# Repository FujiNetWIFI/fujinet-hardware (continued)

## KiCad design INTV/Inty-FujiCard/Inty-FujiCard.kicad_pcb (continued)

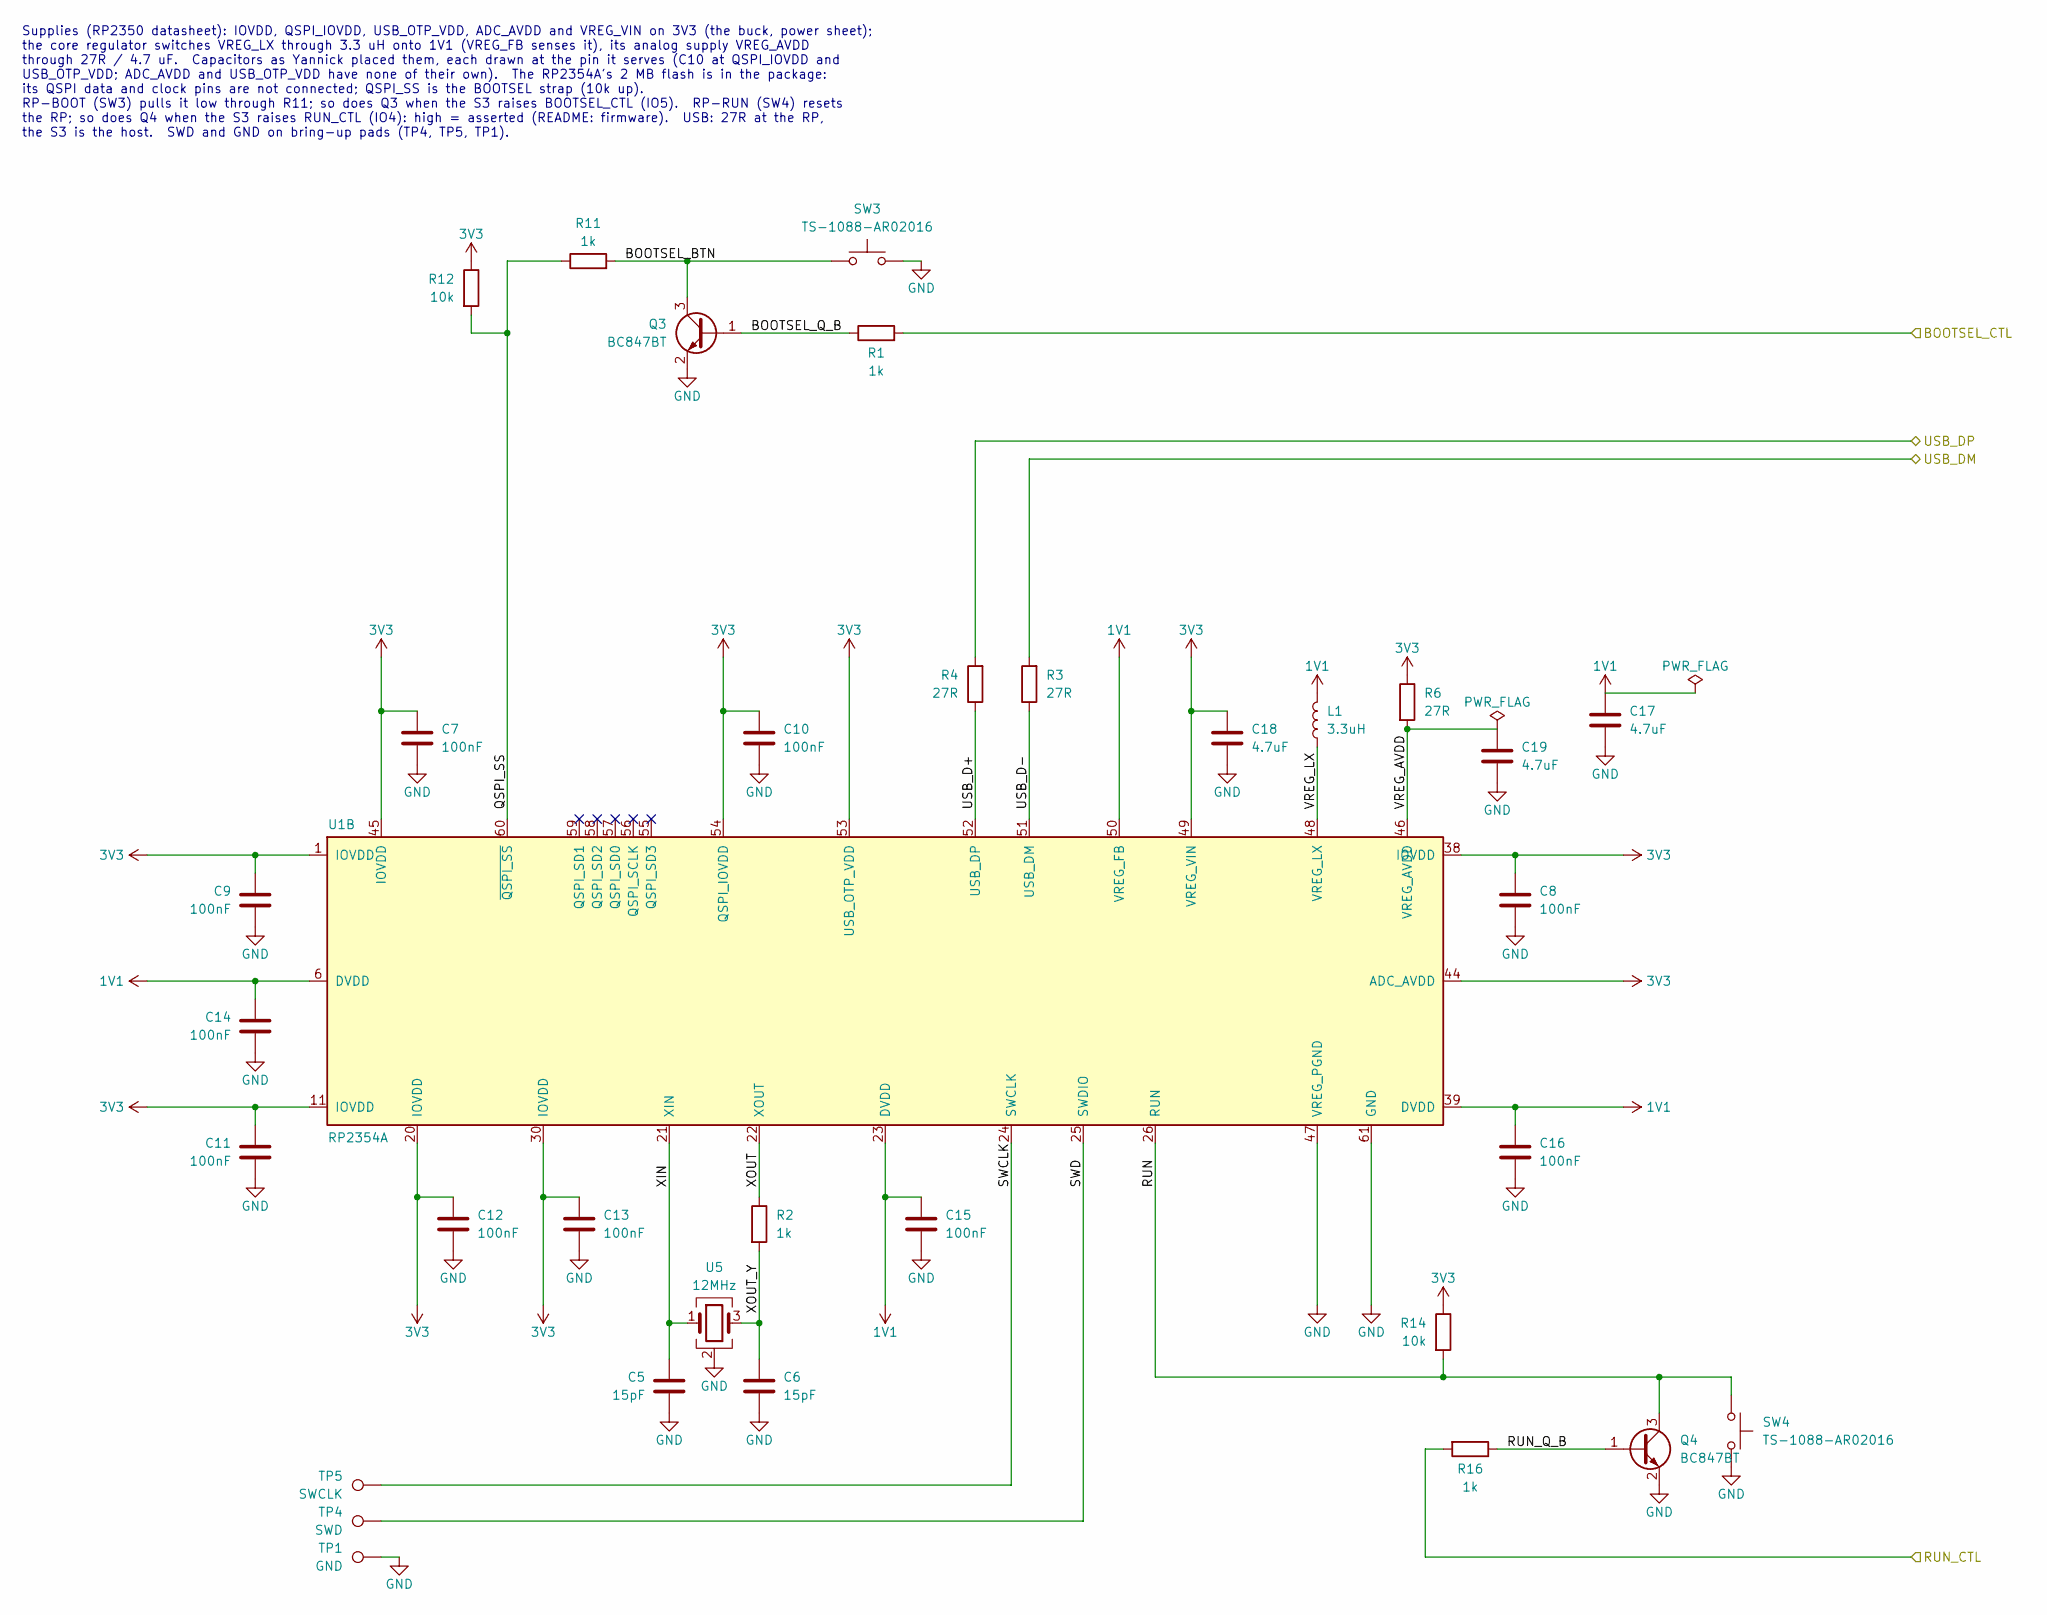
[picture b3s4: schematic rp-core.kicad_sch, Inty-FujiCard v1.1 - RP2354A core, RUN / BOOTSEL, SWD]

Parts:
C5, C6: 15pF; C0402; MPN 0402CG150J500NT; LCSC C1548
C7, C8, C9, C10, C11, C12, C13, C14, C15, C16: 100nF; C0402; MPN CL05B104KO5NNNC; LCSC C1525
C17, C18: 4.7uF; C0603; MPN CL10A475KO8NNNC; LCSC C19666
C19: 4.7uF; C0402; MPN CL05A475MP5NRNC; LCSC C23733
L1: 3.3uH; IND-SMD_L2.0-W1.6_AOTA-B201610S3R3-101-T; MPN AOTA-B201610S3R3-101-T; LCSC C42411119
Q3, Q4: BC847BT; SOT-523-3_L1.6-W0.8-P1.00-LS1.6-BR; MPN BC847BT; LCSC C5186022
R1, R2, R11, R16: 1k; R0402; MPN 0402WGF1001TCE; LCSC C11702
R3, R4, R6: 27R; R0402; MPN 0402WGF270JTCE; LCSC C25100
R12, R14: 10k; R0402; MPN 0402WGF1002TCE; LCSC C25744
SW3, SW4: TS-1088-AR02016; SW-SMD_L3.9-W3.0-P4.45; MPN TS-1088-AR02016; LCSC C720477
TP1: GND; TESTPOINT_PAD_D1.5MM
TP4: SWD; TESTPOINT_PAD_D1.5MM
TP5: SWCLK; TESTPOINT_PAD_D1.5MM
U1: RP2354A; QFN-60_L7.0-W7.0-P0.40-TL-EP3.4; MPN RP2354A; LCSC C41378174
U5: 12MHz; CRYSTAL-SMD_4P-L3.2-W2.5-BL; MPN ABM8-272-T3; LCSC C20625731

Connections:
1V1: C14.2, C15.2, C16.2, C17.2, L1.2, U1.6 (DVDD), U1.23 (DVDD), U1.39 (DVDD), U1.50 (VREG_FB)
3V3: C7.2, C8.2, C9.2, C10.2, C11.2, C12.2, C13.2, C18.2, R6.1, R12.1, R14.1, U1.1 (IOVDD), U1.11 (IOVDD), U1.20 (IOVDD), U1.30 (IOVDD), U1.38 (IOVDD), U1.44 (ADC_AVDD), U1.45 (IOVDD), U1.49 (VREG_VIN), U1.53 (USB_OTP_VDD), U1.54 (QSPI_IOVDD); also elsewhere on the board
/BOOTSEL_CTL: R1.2; also elsewhere on the board
/RUN_CTL: R16.2; also elsewhere on the board
/USB_DM: R3.2; also elsewhere on the board
/USB_DP: R4.2; also elsewhere on the board
/rp-core/BOOTSEL_BTN: Q3.3 (C), R11.2, SW3.1
/rp-core/BOOTSEL_Q_B: Q3.1 (B), R1.1
/rp-core/QSPI_SS: R11.1, R12.2, U1.60 (~QSPI_SS)
/rp-core/RUN: Q4.3 (C), R14.2, SW4.1, U1.26 (RUN)
/rp-core/RUN_Q_B: Q4.1 (B), R16.1
/rp-core/SWCLK: TP5.1, U1.24 (SWCLK)
/rp-core/SWD: TP4.1, U1.25 (SWDIO)
/rp-core/USB_D+: R4.1, U1.52 (USB_DP)
/rp-core/USB_D-: R3.1, U1.51 (USB_DM)
/rp-core/VREG_AVDD: C19.2, R6.2, U1.46 (VREG_AVDD)
/rp-core/VREG_LX: L1.1, U1.48 (VREG_LX)
/rp-core/XIN: C5.2, U1.21 (XIN), U5.1
/rp-core/XOUT: R2.1, U1.22 (XOUT)
/rp-core/XOUT_Y: C6.2, R2.2, U5.3
GND: C5.1, C6.1, C7.1, C8.1, C9.1, C10.1, C11.1, C12.1, C13.1, C14.1, C15.1, C16.1, C17.1, C18.1, C19.1, Q3.2 (E), Q4.2 (E), SW3.2, SW4.2, TP1.1, U1.47 (VREG_PGND), U1.61 (GND), U5.2 (G), U5.4 (G); also elsewhere on the board

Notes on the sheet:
Supplies (RP2350 datasheet): IOVDD, QSPI_IOVDD, USB_OTP_VDD, ADC_AVDD and VREG_VIN on 3V3 (the buck, power sheet); the core regulator switches VREG_LX through 3.3 uH onto 1V1 (VREG_FB senses it), its analog supply VREG_AVDD through 27R / 4.7 uF. Capacitors as Yannick placed them, each drawn at the 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

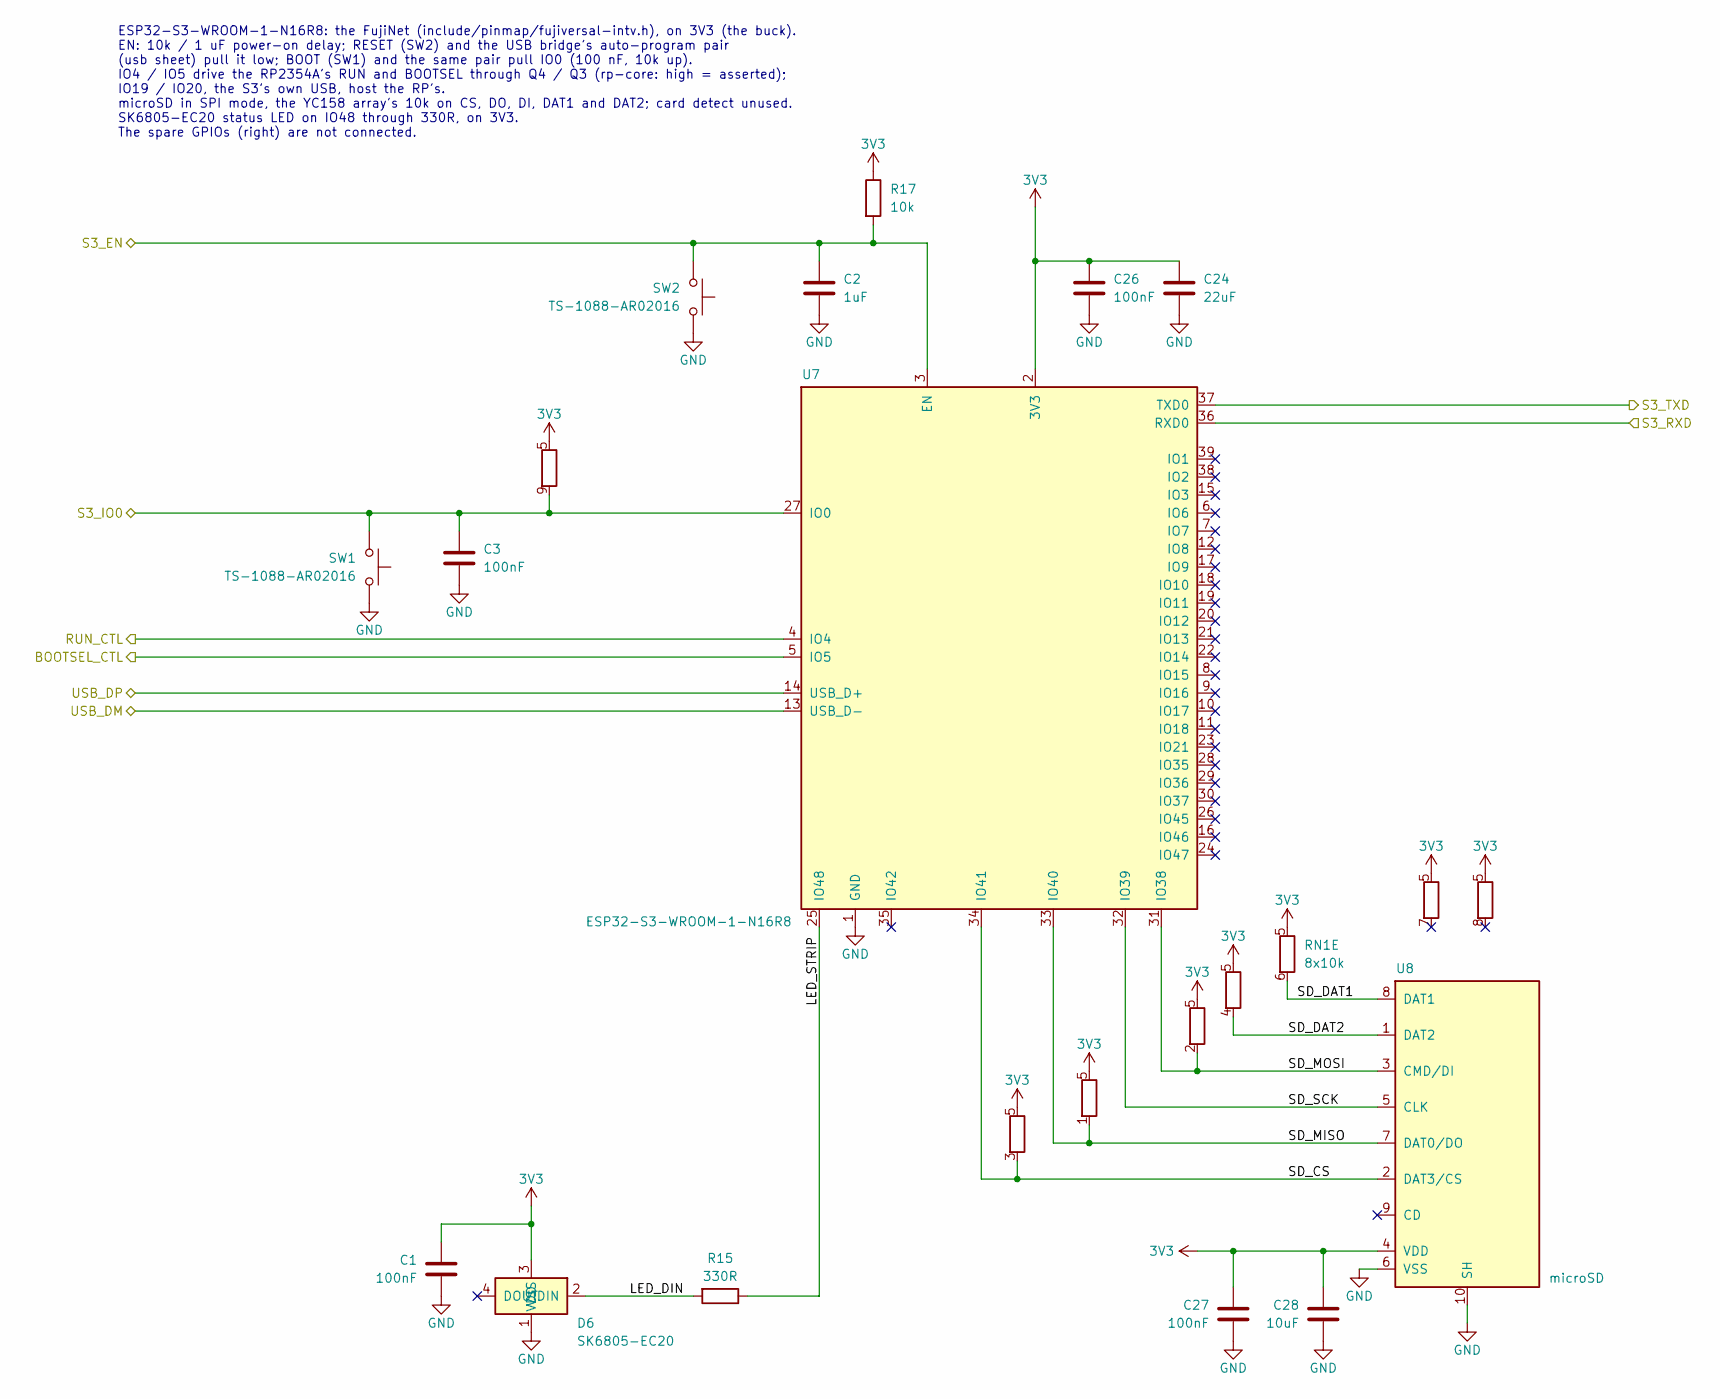
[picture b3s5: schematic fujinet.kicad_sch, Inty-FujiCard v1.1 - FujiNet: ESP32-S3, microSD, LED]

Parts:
C1, C3, C26, C27: 100nF; C0402; MPN CL05B104KO5NNNC; LCSC C1525
C2: 1uF; C0402; MPN CL05A105KA5NQNC; LCSC C52923
C24: 22uF; C0603; MPN CL10A226MQ8NRNC; LCSC C59461
C28: 10uF; C0603; MPN CL10A106KP8NNNC; LCSC C19702
D6: SK6805-EC20; LED-SMD_4P-L2.0-W2.0-TL_J-ST2020RGB-IC-P4-5-SO1; MPN SK6805-EC20; LCSC C2890036
R15: 330R; R0402; MPN 0402WGF3300TCE; LCSC C25104
R17: 10k; R0402; MPN 0402WGF1002TCE; LCSC C25744
RN1: 8x10k; RES-ARRAY-SMD_1206-L3.2-W1.6-P0.64; MPN YC158TJR-0710KL; LCSC C309679
SW1, SW2: TS-1088-AR02016; SW-SMD_L3.9-W3.0-P4.45; MPN TS-1088-AR02016; LCSC C720477
U7: ESP32-S3-WROOM-1-N16R8; WIRELM-SMD_ESP32-S3-WROOM-1; MPN ESP32-S3-WROOM-1-N16R8; LCSC C2913202
U8: microSD; SIM-SMD_LX_XDFP-0090-012; MPN TF-CARD-9P; LCSC C53144700

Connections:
3V3: C1.2, C24.2, C26.2, C27.2, C28.1, D6.3 (VDD), R17.1, RN1.5 (COM), RN1.10 (COM), U7.2 (3V3), U8.4 (VDD); also elsewhere on the board
/BOOTSEL_CTL: U7.5 (IO5); also elsewhere on the board
/RUN_CTL: U7.4 (IO4); also elsewhere on the board
/S3_EN: C2.2, R17.2, SW2.1, U7.3 (EN); also elsewhere on the board
/S3_IO0: C3.2, RN1.9 (R8), SW1.1, U7.27 (IO0); also elsewhere on the board
/S3_RXD: U7.36 (RXD0); also elsewhere on the board
/S3_TXD: U7.37 (TXD0); also elsewhere on the board
/USB_DM: U7.13 (USB_D-); also elsewhere on the board
/USB_DP: U7.14 (USB_D+); also elsewhere on the board
/fujinet/LED_DIN: D6.2 (DIN), R15.2
/fujinet/LED_STRIP: R15.1, U7.25 (IO48)
/fujinet/SD_CS: RN1.3 (R3), U7.34 (IO41), U8.2 (DAT3/CS)
/fujinet/SD_DAT1: RN1.6 (R5), U8.8 (DAT1)
/fujinet/SD_DAT2: RN1.4 (R4), U8.1 (DAT2)
/fujinet/SD_MISO: RN1.1 (R1), U7.33 (IO40), U8.7 (DAT0/DO)
/fujinet/SD_MOSI: RN1.2 (R2), U7.31 (IO38), U8.3 (CMD/DI)
/fujinet/SD_SCK: U7.32 (IO39), U8.5 (CLK)
GND: C1.1, C2.1, C3.1, C24.1, C26.1, C27.1, C28.2, D6.1 (VSS), SW1.2, SW2.2, U7.1 (GND), U7.40 (GND), U7.41 (GND), U8.6 (VSS), U8.10 (SH); also elsewhere on the board

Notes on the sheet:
ESP32-S3-WROOM-1-N16R8: the FujiNet (include/pinmap/fujiversal-intv.h), on 3V3 (the buck). EN: 10k / 1 uF power-on delay; RESET (SW2) and the USB bridge's auto-program pair (usb sheet) pull it low; BOOT (SW1) and the same pair pull IO0 (100 nF, 10k up). IO4 / IO5 drive the RP2354A's RUN and BOOTSEL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

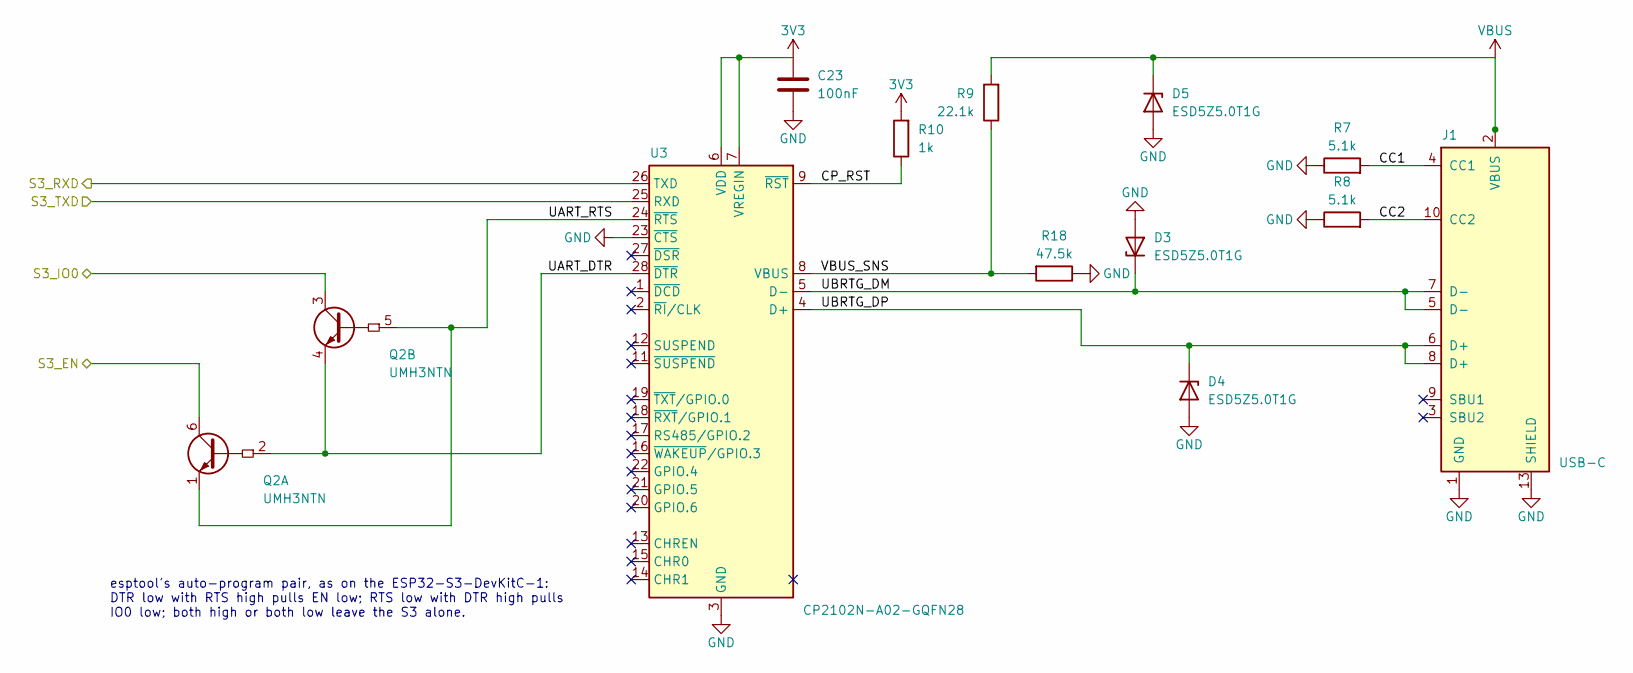
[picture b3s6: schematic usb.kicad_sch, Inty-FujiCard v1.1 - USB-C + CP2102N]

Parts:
C23: 100nF; C0402; MPN CL05B104KO5NNNC; LCSC C1525
D3, D4, D5: ESD5Z5.0T1G; SOD-523_L1.2-W0.8-LS1.6-RD; MPN ESD5Z5.0T1G; LCSC C343989
J1: USB-C; USB-C-SMD_TYPE-C-6PIN-2MD-073; MPN TYPE-C 16PIN 2MD(073); LCSC C2765186
Q2: UMH3NTN; SOT-363_L2.0-W1.3-P0.65-LS2.1-TL; MPN UMH3NTN; LCSC C123008
R7, R8: 5.1k; R0402; MPN 0402WGF5101TCE; LCSC C25905
R9: 22.1k; R0402; MPN AC0402FR-0722K1L; LCSC C226356
R10: 1k; R0402; MPN 0402WGF1001TCE; LCSC C11702
R18: 47.5k; R0402; MPN RC0402FR-0747K5L; LCSC C137974
U3: CP2102N-A02-GQFN28; QFN-28_L5.0-W5.0-P0.50-TL-EP3.3; MPN CP2102N-A02-GQFN28R; LCSC C964632

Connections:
3V3: C23.2, R10.2, U3.6 (VDD), U3.7 (VREGIN); also elsewhere on the board
/S3_EN: Q2.6 (C1); also elsewhere on the board
/S3_IO0: Q2.3 (C2); also elsewhere on the board
/S3_RXD: U3.26 (TXD); also elsewhere on the board
/S3_TXD: U3.25 (RXD); also elsewhere on the board
/usb/CC1: J1.4 (CC1), R7.2
/usb/CC2: J1.10 (CC2), R8.2
/usb/CP_RST: R10.1, U3.9 (~RST)
/usb/UART_DTR: Q2.2 (B1), Q2.4 (E2), U3.28 (~DTR)
/usb/UART_RTS: Q2.1 (E1), Q2.5 (B2), U3.24 (~RTS)
/usb/UBRTG_DM: D3.1 (K), J1.5 (D-), J1.7 (D-), U3.5 (D-)
/usb/UBRTG_DP: D4.1 (K), J1.6 (D+), J1.8 (D+), U3.4 (D+)
/usb/VBUS_SNS: R9.1, R18.2, U3.8 (VBUS)
GND: C23.1, D3.2 (A), D4.2 (A), D5.2 (A), J1.1 (GND), J1.12 (GND), J1.13 (SHIELD), J1.14 (SHIELD), R7.1, R8.1, R18.1, U3.3 (GND), U3.23 (~CTS), U3.29 (GND); also elsewhere on the board
VBUS: D5.1 (K), J1.2 (VBUS), J1.11 (VBUS), R9.2; also elsewhere on the board

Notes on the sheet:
esptool's auto-program pair, as on the ESP32-S3-DevKitC-1: DTR low with RTS high pulls EN low; RTS low with DTR high pulls IO0 low; both high or both low leave the S3 alone.

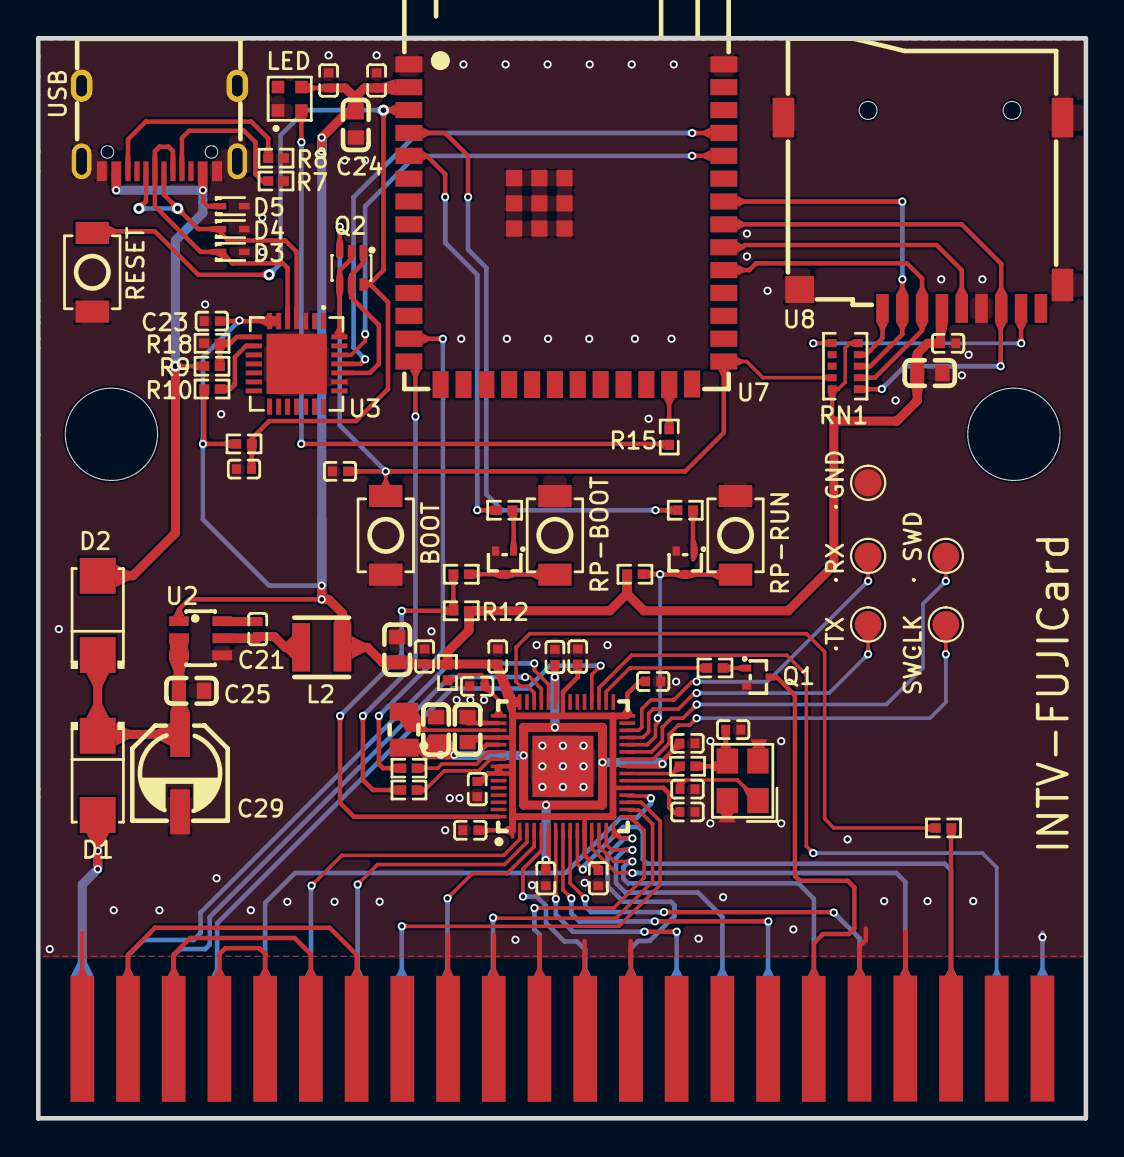
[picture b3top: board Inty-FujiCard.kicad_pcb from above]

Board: 2 copper layers, 58.2 x 60.0 mm, 78 parts (0 on the bottom side), 76 nets.

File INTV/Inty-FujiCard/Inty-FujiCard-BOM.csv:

Qty,References,Value,Footprint,MPN,Manufacturer,LCSC,Description,Notes
17,C1 C3 C7 C8 C9 C10 C11 C12 C13 C14 C15 C16 C21 C22 C23 C26 C27,100nF,C0402,CL05B104KO5NNNC,SAMSUNG,C1525,capacitor (several uses: see schematic),
1,C2,1uF,C0402,CL05A105KA5NQNC,SAMSUNG,C52923,EN power-on delay,
2,C4 C24,22uF,C0603,CL10A226MQ8NRNC,SAMSUNG,C59461,capacitor (several uses: see schematic),
2,C5 C6,15pF,C0402,0402CG150J500NT,FH,C1548,crystal load,
2,C17 C18,4.7uF,C0603,CL10A475KO8NNNC,SAMSUNG,C19666,capacitor (several uses: see schematic),
1,C19,4.7uF,C0402,CL05A475MP5NRNC,SAMSUNG,C23733,VREG_AVDD RC filter (C_FILT),
2,C25 C28,10uF,C0603,CL10A106KP8NNNC,SAMSUNG,C19702,capacitor (several uses: see schematic),
1,C29,100uF,CAP-SMD_BD5.0-L5.3-W5.3-RD,VE-101M1ATR-0505,Lelon,C134722,VIN bulk,
2,D1 D2,SS34,SMA_L4.3-W2.6-LS5.2-RD,SS34,MDD,C8678,diode (several uses: see schematic),
3,D3 D4 D5,ESD5Z5.0T1G,SOD-523_L1.2-W0.8-LS1.6-RD,ESD5Z5.0T1G,BORN,C343989,diode (several uses: see schematic),
1,D6,SK6805-EC20,LED-SMD_4P-L2.0-W2.0-TL_J-ST2020RGB-IC-P4-5-SO1,SK6805-EC20,OPSCO Optoelectronics,C2890036,"status LED (IO48), on 3V3",
2,H1 H2,Hole_D5.127mm,Hole_D5.127mm_NPTH,,,,"shell post hole, 5.127 mm NPTH",not in BOM
1,J1,USB-C,USB-C-SMD_TYPE-C-6PIN-2MD-073,TYPE-C 16PIN 2MD(073),SHOU HAN,C2765186,power + S3 programming / console,
1,K1,INTV_Cart_Edge_44,PCB_EDGE_CONNECTOR_22X2,,,,"Intellivision cartridge edge, 2 x 22 gold fingers, 2.54 mm: A1-A22 component face, B1-B22 back",not in BOM
1,L1,3.3uH,IND-SMD_L2.0-W1.6_AOTA-B201610S3R3-101-T,AOTA-B201610S3R3-101-T,ABRACON,C42411119,RP2350 core SMPS inductor,
1,L2,4.7uH,IND-SMD_L3.0-W3.0-1,YNR3015-4R7M,YJYCOIN,C340361,buck inductor,
3,Q1 Q3 Q4,BC847BT,SOT-523-3_L1.6-W0.8-P1.00-LS1.6-BR,BC847BT,Slkor,C5186022,transistor (several uses: see schematic),
1,Q2,UMH3NTN,SOT-363_L2.0-W1.3-P0.65-LS2.1-TL,UMH3NTN,ROHM,C123008,esptool auto-program (DevKitC-1 style),
7,R1 R2 R5 R10 R11 R13 R16,1k,R0402,0402WGF1001TCE,UNI-ROYAL,C11702,resistor (several uses: see schematic),
3,R3 R4 R6,27R,R0402,0402WGF270JTCE,UNI-ROYAL,C25100,resistor (several uses: see schematic),
2,R7 R8,5.1k,R0402,0402WGF5101TCE,UNI-ROYAL,C25905,resistor (several uses: see schematic),
1,R9,22.1k,R0402,AC0402FR-0722K1L,YAGEO,C226356,VBUS sense divider,
3,R12 R14 R17,10k,R0402,0402WGF1002TCE,UNI-ROYAL,C25744,resistor (several uses: see schematic),
1,R15,330R,R0402,0402WGF3300TCE,UNI-ROYAL,C25104,status LED data series,
1,R18,47.5k,R0402,RC0402FR-0747K5L,YAGEO,C137974,VBUS sense divider,
1,RN1,8x10k,RES-ARRAY-SMD_1206-L3.2-W1.6-P0.64,YC158TJR-0710KL,YAGEO,C309679,"pull-ups: microSD lines, S3 IO0",
4,SW1 SW2 SW3 SW4,TS-1088-AR02016,SW-SMD_L3.9-W3.0-P4.45,TS-1088-AR02016,XUNPU,C720477,push button (several uses: see schematic),
1,TP1,GND,TESTPOINT_PAD_D1.5MM,,,,test pad: GND,not in BOM
1,TP2,TX,TESTPOINT_PAD_D1.5MM,,,,test pad: GP16 (silk TX),not in BOM
1,TP3,RX,TESTPOINT_PAD_D1.5MM,,,,test pad: GP17 (silk RX),not in BOM
1,TP4,SWD,TESTPOINT_PAD_D1.5MM,,,,test pad: SWDIO,not in BOM
1,TP5,SWCLK,TESTPOINT_PAD_D1.5MM,,,,test pad: SWCLK,not in BOM
1,U1,RP2354A,QFN-60_L7.0-W7.0-P0.40-TL-EP3.4,RP2354A,Raspberry Pi,C41378174,RP2354A: serves the Intellivision cartridge bus (fujicard),
1,U2,AP63203WU,TSOT-26_L2.9-W1.6-P0.95-LS2.8-BL,AP63203WU-7,DIODES,C780769,3.3V 2A buck: the whole board,
1,U3,CP2102N-A02-GQFN28,QFN-28_L5.0-W5.0-P0.50-TL-EP3.3,CP2102N-A02-GQFN28R,SKYWORKS/SILICON LABS,C964632,USB-UART for S3 flashing / console (self-powered),
1,U5,12MHz,CRYSTAL-SMD_4P-L3.2-W2.5-BL,ABM8-272-T3,ABRACON,C20625731,RP2354A 12 MHz crystal,
1,U7,ESP32-S3-WROOM-1-N16R8,WIRELM-SMD_ESP32-S3-WROOM-1,ESP32-S3-WROOM-1-N16R8,ESPRESSIF,C2913202,FujiNet core (fujiversal-intv),
1,U8,microSD,SIM-SMD_LX_XDFP-0090-012,TF-CARD-9P,BXCONN,C53144700,"microSD push-push, SPI mode (card detect unused)",

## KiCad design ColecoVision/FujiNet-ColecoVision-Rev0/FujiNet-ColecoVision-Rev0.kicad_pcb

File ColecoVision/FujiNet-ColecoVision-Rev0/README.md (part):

# FujiNet-ColecoVision Rev0

FujiNet for the ColecoVision (and the ADAM's cartridge slot), on one cartridge.
- **RP2350A + W25Q16:** serves the Z80's cartridge bus (`fujinet-firmware/pico/coleco`): A0-A14 straight off the 5 V edge, D0-D7 through a 74LVC245A whose /OE is the AND of the four cart selects.
- **ESP32-S3:** the FujiNet (`fujiversal-coleco`) and the RP's USB host, on the same board.
- **Also on the board:** a microSD, a WS2812 status light, and a USB-C with a CP2102N bridge for flashing and powering it.

**Status (2026-11-05): board routed on 4 layers, JLCPCB and PCBWay packages generated, every gate passing. Nothing has been built yet.**
- **Board:** 4 layers, 40.2 x 82.4 mm, the ColecoVision cart outline (the whole bottom edge carries 2 x 15 gold fingers), four side notches for the shell's ribs. Assembled by JLCPCB or PCBWay, top side only.
- **Firmware:** the schematic implements `pico/coleco/firmware/include/coleco_cart.h` as it stands on fujinet-firmware master. The board file and S3 pin map it still needs are under *Firmware changes this board needs*.
- **Edge:** checked against MAME's slot table and two built, open carts (`tools/audit/edge_orientation.py`); not provisional.
- **Shell:** fits a printed shell (`case/`). An original Coleco shell is unverified: see *Original shell*.

| Check (2026-11-05) | Result |
|---|---|
| Drawing checks (`gen_sch.py`) | every sheet wired; 0 crossings on `cart-bus`, `rp-core`, `fujinet`, `power`; 1 on `usb` (esptool's auto-program pair, as on Studio II and the O2) |
| Netlist parity: kicad-cli netlist vs `design.py`, names included | 112 / 112 nets |
| KiCad ERC, all severities | 0 errors, 0 warnings |
| `tools/check_nets.py`: the netlist vs `coleco_cart.h`, `fujiversal-coleco.h` (fujinet-firmware `origin/master`) | 390 checks, 0 failed; 3 NOTE lines (the firmware changes below) |
| `tools/audit/edge_orientation.py`: footprint and netlist vs MAME's slot table, ThatOldNerd's and Commodore-Bench's boards | all pass (`VERIFIED = True`) |
| `tools/audit/margins.py`: Z80 / LS138 levels against the 330R, the LVC parts and the RP, the select-to-buffer timing, VSENSE, the mux threshold, the cart's draw | 0 negative margins (tightest: +0.11 V, the mux's VBUS threshold under a 4.75 V USB source) |
| Routing | 100 % on 4 layers (see *Layout*); 390 vias, 1136 tracks |
| KiCad DRC + schematic parity on the saved zone fills (kicad-cli, and again through the KiCad MCP) | 0 errors, 0 unconnected, 0 parity issues; 3 silk-over-edge warnings (the S3 module's outline at the flush west edge) |
| `tools/check_vias.py`: no via in a foreign SMD pad | 378 vias, 0 failures |
| `tools/audit/layout_checks.py`: the layout's claims measured on the copper | 56 / 56 (regulator corner, decoupling, USB pairs and skew, crystal, QSPI, exposed pads, every finger to its part in at most 4 vias, the CONS_5V island, the S3 antenna strip, the buck loop) |
| `tools/audit/check_gerbers.py`: the zip itself | 0 failures: outline and notches, both finger rows, masks, inner layers, no plated hole inside an In1 / In2 pour of another net (403 holes) |
| `tools/audit/check_fab.py`: JLC and PCBWay BOM / CPL / centroid / drills / order-number text / gerbers / the edge gate | all pass |
| JLCPCB CPL rotations (`tools/audit/jlc/`), measured against each LCSC part's EasyEDA footprint | 43 (footprint, LCSC) pairs, the RP2350A's QFN-60 high-confidence; 6 medium (the two AND gates, AOTA inductor, TS-1187A, BAT54C, USB-C): check them in JLC's preview |
| kicad-happy 2.2.1 (`tools/audit/run_sch_audit.sh`, `run_pcb_audit.sh`), triaged in `docs/design-review-rev0.md` | SPICE 14 / 14; 8 high-rule groups: 3 false positives or by design (keep-out boxes, the fiducial and connectors at the edge, UMH3N decoupling), 1 not a split (+3V3_RP fills as one piece), 3 accepted or minor (bus over In2 island edges, USB layer changes, the USB pair across islands), 1 minor (the USBLC6's VBUS cap 9 mm away) |
| Printed shell (`case/`, OpenSCAD) | `check` and `parts_check` empty, `parts_control` 86 volumes |

## Sheets

Drawn with the FujiNet-StudioII / Arcadia / O2 toolkit:
- **Wires only:** every connection on a sheet is a wire.
- **Rails:** rails are power symbols (`GND`, `CONS_5V`, `VBUS`, `+5V`, `+3V3`, `+3V3_RP`, `DVDD`).
- **Between sheets:** the sheets join only through hierarchical labels, wired on the root's block diagram.

| Page | Sheet | Contents |
|---|---|---|
| 1 | root | the block diagram: rp-core <-> fujinet (USB_DP / USB_DM, RUN_CTL, BOOTSEL_CTL, S3_EN), fujinet <-> usb (S3_TXD / S3_RXD, S3_EN, S3_IO0); notes |
| 2 | `cart-bus` | the 30-finger edge and the RP2350A's GPIO unit row for row: A0-A14 straight through the four 330R arrays; D0-D7 straight through the 74LVC245A; DIR (GP27) from the buffer's foot with its pull-up; the four selects, pulled up, into the 74LVC1G11 + 74LVC1G08, whose /CE rises into the buffer's /OE and runs on to GP26; the console-5V sense (GP28), the activity LED (GP25), the bring-up pads (GP23, GP24, GP29) |
| 3 | `rp-core` | the RP2350A's core unit: a capacitor at every supply pin, Raspberry Pi's regulator corner, the W25Q16 standing over the QSPI pins, crystal, SWD, RUN / BOOTSEL / RESET (the BAT54C to S3 EN), the USB 27R pair out to the S3 |
| 4 | `fujinet` | ESP32-S3-WROOM-1-N16R8, its EN RC and BOOT button, microSD, WS2812 |
| 5 | `usb` | USB-C, USBLC6-2SC6, CP2102N, esptool's auto-program pair |
| 6 | `power` | TPS2116 power mux (USB first, console 5 V second), the S3's AP63203 buck, the RP's AP2112K LDO, rail test pads |

## Edge connector

30 contacts in two rows of 15 at 2.54 mm. The **even pins** are on the component face, the **odd pins** behind them (pin 1 behind pin 2). Seen from the component face with the contacts down, pins 1 / 2 are at the left.

| Pin | Signal | Board net | Pin | Signal | Board net |
|---|---|---|---|---|---|
| 1, 3, 5 | D2, D1, D0 | '245 A2, A1, A0 | 2 | /C000 | 10k up; 74LVC1G11 |
| 7, 9, 11 | A0, A1, A2 | 330R -> GP0-2 | 4-12 | D3-D7 | '245 A3-A7 |
| 13 | SHLD (ADAM: RF ground) | GND | 14, 16 | A11, A10 | 330R -> GP11, GP10 |
| 15, 17 | A3, A4 | 330R -> GP3, GP4 | 18 | /8000 | 10k up; 74LVC1G11 |
| 19 | A13 | 330R -> GP13 | 20 | A14 | 330R -> GP14 |
| 21-25 | A5, A6, A7 | 330R -> GP5-7 | 22 | /A000 | 10k up; 74LVC1G11 |
| 27 | /E000 | 10k up; 74LVC1G08 | 24, 26, 28 | A12, A9, A8 | 330R -> GP12, GP9, GP8 |
| 29 | GND | GND | 30 | +5V | CONS_5V -> TPS2116 VIN2 (this finger starts 1.5 mm in: it mates last) |

No /RD, /WR, A15, clock or reset reach the cart. The selects come from the console's '138, enabled by /MREQ and RFSH: a write selects as a read does, refresh never.

**Sources:**
- **Pinout:** MAME `src/devices/bus/coleco/cartridge/exp.h`, the same as the Coleco ADAM Technical Reference Manual's J1 (CS1*-CS4* = /8000 /A000 /C000 /E000).
- **Two built, open carts**, read from their design files (numbers and names only, no file copied): ThatOldNerd's Coleco-Game-Cart V4 (GPL-3.0, Eagle) and Commodore-Bench's ColecoVision Reprogrammable Flash Card (MIT, KiCad; aotta's PiCOLECO uses the same footprint). Joe Grand's "Pixels Past" cart ("fits standard housing") for the width and the notches.
- `tools/audit/edge_orientation.py` checks the footprint and the netlist against all of them (and a local MAME tree when there is one). It passes, so `tools/edge_geom.VERIFIED` is True.

**Geometry (`tools/edge_geom.py`):**
- 15 fingers per face at 2.54 mm, 1.6 mm wide, from 0.5 mm in (the bevel) to 8.5 mm; the +5V finger from 1.5 mm (Commodore-Bench's practice: GND mates first); 1.6 mm board (the slot takes 1.57 +- 0.2 mm);
- the 40.2 x 82.4 mm outline: built carts are 40.0-40.64 wide; Commodore-Bench's / PiCOLECO's length, so the USB-C and the microSD reach the shell's top wall;
- four 2.0 mm side notches at the widest published spans (ThatOldNerd's): 19.6-26.0 mm up on both sides, 34.0-40.5 (pin-1 side) and 36.5-43.0 (pin-30 side);
- no part closer than 15 mm to the edge (ThatOldNerd's lowest pads sit at 15, Commodore-Bench's lowest parts at 17).

## RP2350A pin map

Exactly `coleco_cart.h`. `tools/check_nets.py` reads it from fujinet-firmware `origin/master` and checks every pin.

| GPIO | Net | Goes to |
|---|---|---|
| 0-14 | RP_A0-14 | 330R -> A0-A14 (`ADDR_MASK` 0x7FFF; 5 V-tolerant pads) |
| 15-22 | RP_D0-7 | the 74LVC245A's B port (`D0_PIN` 15) |
| 23 | GP23 | test pad (spare) |
| 24 | DBG_TX | test pad, UART1 TX, 3.3 V |
| 25 | RP_LED | 680R, red LED (`PICO_DEFAULT_LED_PIN`) |
| 26 | CART_CE_N | the AND of /8000 /A000 /C000 /E000 (`CE_PIN`), also the '245's /OE |
| 27 | BUF_DIR | the '245's DIR, 1 = console -> cart (`DIR_PIN`), 10k pull-up |
| 28 | VSENSE | console 5 V through 10k / 15k (3.0 V at 5 V), 100 nF (`PWR_PIN`, read as a digital input) |
| 29 | SELFTEST | test pad |
| QSPI | QSPI_SS / SCLK / SD0-3 | W25Q16JV (2 MB), its /CS the BOOTSEL strap |
| USB | RP_USB_DP / DM | 27R -> the ESP32-S3's USB host (IO20 / IO19), on the board |
| RUN, QSPI_SS | | 10k pull-ups; RESET / BOOTSEL buttons; 1k from S3 IO4 / IO5 |

**The bus side.** core1 drives GP15-22 off the bare address on every cycle, RAM and BIOS cycles included (`coleco_cart.c`), so the data buffer's /OE must be the hardware select: the 74LVC1G11 + 74LVC1G08 AND the four selects (no 74LVC21 is stocked at JLCPCB). The '245 and the gates run at 3.3 V with 5 V-tolerant inputs (`coleco_cart.h` asks for an LVC part, not HCT). DIR's pull-up keeps the buffer facing the RP while the RP is in reset, and the firmware holds it there while the console is off (its unpowered '138 reads as every select low). `tools/audit/margins.py` has the levels and the timing (the gates and the buffer's enable add under 30 ns against the ~285 ns the firmware has after /CE falls).

**Why the RP2350A + W25Q16:** on 2026-11-04 the RP2354A (C41378174) and RP2354B (C39843328), the stacked-flash parts the sister carts use, were out of stock at JLCPCB and LCSC; the RP2350A (C42411118) and the W25Q16JVUXIQ (C2843335) were in stock. The QFN-60's GPIO0-25 are 5 V tolerant; GP26-28 (/CE, DIR, PWR) only ever see 3.3 V. The RP2350's 520 KB SRAM lifts the firmware's 128K image cap (an RP2040 limit).

## ESP32-S3 pin map

`include/pinmap/fujiversal-coleco.h` (SD 38-41, UART0 43/44, LED strip 48), plus what every on-cart S3 board adds:

| S3 pin | Net | Goes to |
|---|---|---|
| IO19 / IO20 | USB_DM / USB_DP | the RP2350A's USB through its 27R (the S3 is the host) |
| IO38 / 39 / 40 / 41 | SD_MOSI / SCK / MISO / CS | microSD (SPI), 10k pull-ups on CS, DO, DAT1, DAT2 |
| IO42 | SD_CD | card detect, 10k pull-up (low = card in) |
| IO48 | LED_STRIP | 330R -> WS2812B-2020 (on +5V; VIH 2.7 V takes 3.3 V data) |
| TXD0 / RXD0 | S3_TXD / S3_RXD | CP2102N |
| IO4 / IO5 | RUN_CTL / BOOTSEL_CTL | 1k -> RP RUN / QSPI_SS: the S3 can reset the RP into its USB boot ROM |
| EN / IO0 | S3_EN / S3_IO0 | EN RC (10k / 1 uF), RESET (through the BAT54C), the BOOT button, the auto-program pair |

There is no separate S3 EN button (the sister carts have one): RESET pulls EN low through the BAT54C, and the 40 mm board has no room for a fourth switch.

## Power

| Rail | Source | Feeds |
|---|---|---|
| `CONS_5V` | edge pin 30 (the console's 5 V) | TPS2116 VIN2, the VSENSE divider |
| `VBUS` | USB-C (USBLC6, 1 uF + 100 nF) | TPS2116 VIN1 (priority), CP2102N VBUS sense |
| `+5V` | **TPS2116 mux**: VBUS above 3.96-4.64 V first (MODE on VIN1, PR1 33k / 10k), else the console | the buck, the RP LDO, the WS2812 |
| `+3V3` | AP63203 3.3 V / 2 A buck | ESP32-S3, CP2102N, microSD |
| `+3V3_RP` | AP2112K-3.3 LDO | every RP2350A supply pin, the W25Q16, the 74LVC245A and the AND gates |
| `DVDD` | RP2350 core SMPS (3.3 uH) | RP core, 1.1 V |

**Load:** without USB, ~145 mA average and ~370 mA in WiFi bursts at 5 V (`margins.py`). The ADAM's Technical Reference Manual rates its cart slot at "typical available current 0.2A"; the ColecoVision's figure is not published. **Prefer USB-C power during play.** The mux blocks reverse current both ways: a cart on USB never powers a console that is off.

## Layout

- **Stack (4 layers, JLC04161H-7628):** F.Cu signals + GND pour (even fingers); In1 GND; In2 +5V with a +3V3 island (the upper half: module, CP2102N, microSD, buck output, and a tongue under the module's foot for its decoupling), a +3V3_RP island (the lower half: RP, flash, bus logic, LDO output), a DVDD island under the RP's core, and a CONS_5V strip from the +5V finger up the east edge to the mux; B.Cu signals + GND pour (odd fingers). Inner planes stop above the finger field; the finger field is a rule area on both faces.
- **Placement (`tools/placement.py`):**
  - **Top edge:** the USB-C (west of centre) and the microSD (east), both reaching the shell's top wall; the CP2102N block between the USB-C and the module.
  - **Upper body:** the ESP32-S3 turned 90 degrees, its antenna flush with the west edge over a strip that is copper-free on every layer, 15 mm either side of the module's centre line (the footprint's own keep-out is 24 mm: narrowed here, the board is 40 mm wide); east of it the buck, RESET and S3 BOOT, the WS2812.
  - **Lower body:** the RP2350A at 90 degrees in FujiNet-Arcadia Rev0's neighbourhood (decoupling north, crystal east, Raspberry Pi's regulator corner west, turned with it), the W25Q16 west of it where Raspberry Pi's minimal design has its flash; the four address arrays under it in GPIO order, inputs toward the fingers; the 74LVC245A in the south-west corner, straight over the data fingers (the edge's D0-D7 are its west end; GP15-22's lines cross under the address lines); the select pull-ups and the AND pair east of the arrays, with the bring-up pads; the mux by the +5V finger's column; BOOTSEL on the west edge.
  - **Band above the fingers (y 115-120.5):** parts-free (the shell's bottom). It carries the buses.
- **Deterministic copper:** Raspberry Pi's regulator corner (`tools/rpi_core_graft.sexpr`) and the under-package +3V3_RP bar / DVDD vias (`gen_pcb.rp_ring`, FujiNet-Arcadia Rev0's); the finger neck vias (the +5V finger's into the CONS_5V island, 1.6 mm above the GND finger's behind it); the TPS2116's under-body joins (`gen_pcb.mux_link`); the CP2102N's VDD / VREGIN join (`gen_pcb.uart_link`), clear of D-'s entry.
- **Routing order** (`tools/route_board.sh`):
  1. the 27 edge nets and the USB pair, with the grid router, locked (`placement.PRE_ROUTE`): Freerouting never enters a finger's neck;
  2. the W25Q16's six QSPI lines alone in Freerouting, locked (`placement.FR_FIRST`, `tools/fr_subset.py`): in the full run, B.Cu through-traffic crosses the flash corner and walls one of them out;
  3. Freerouting, then the grid router for what it leaves.

**Rev0 compromises** (measured; `docs/design-review-rev0.md`):
- **QSPI_SD2 / QSPI_SS** go round the W25Q16's far row: 22 and 24 mm against SCLK's 9.5 mm (about 90 ps).
- **Decoupling:** the W25Q16's 100 nF is 6.3 mm from VCC, the CP2102N's 6.2 mm; the buck's 100 nF 6.4 mm from VIN (its 22 uF at 3.3 mm).
- **RP_A1** is laid by hand between RP_A0 and RP_A2 (0.15 mm): no router run joined it.
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
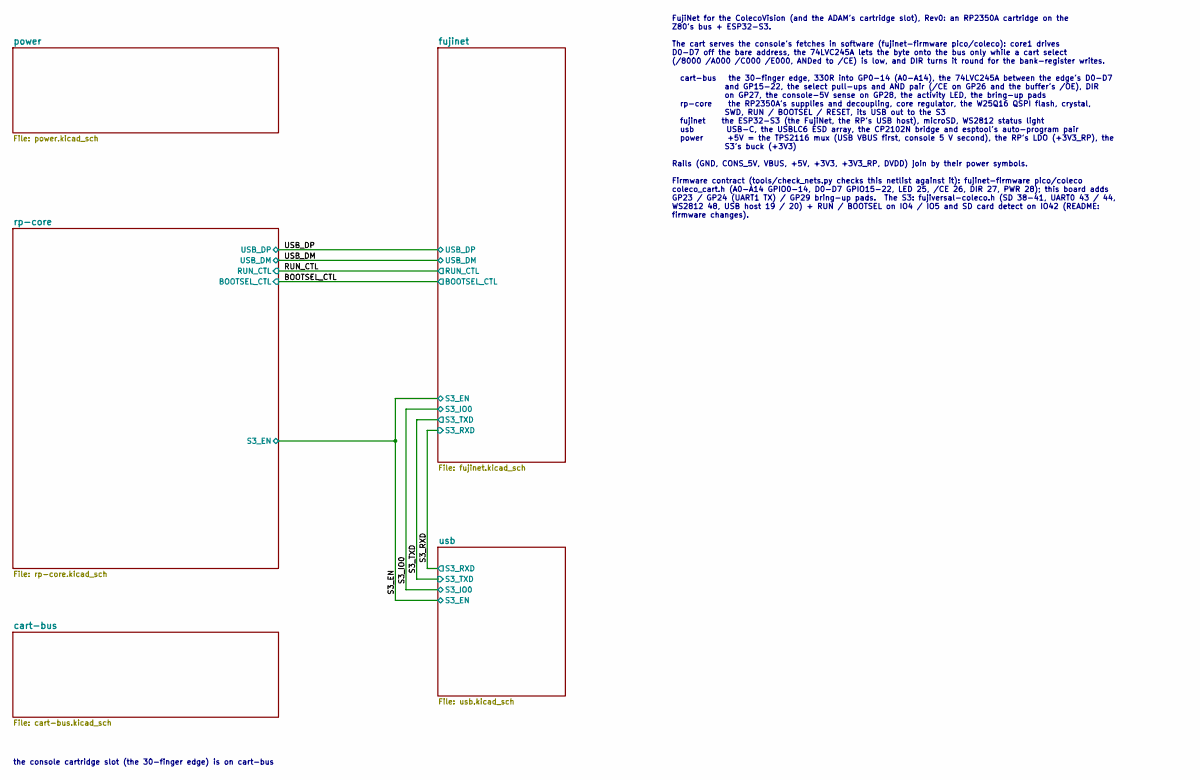
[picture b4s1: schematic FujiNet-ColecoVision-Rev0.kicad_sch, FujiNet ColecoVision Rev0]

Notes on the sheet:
the console cartridge slot (the 30-finger edge) is on cart-bus
FujiNet for the ColecoVision (and the ADAM's cartridge slot), Rev0: an RP2350A cartridge on the Z80's bus + ESP32-S3. The cart serves the console's fetches in software (fujinet-firmware pico/coleco): core1 drives D0-D7 off the bare address, the 74LVC245A lets the byte onto the bus only while a cart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

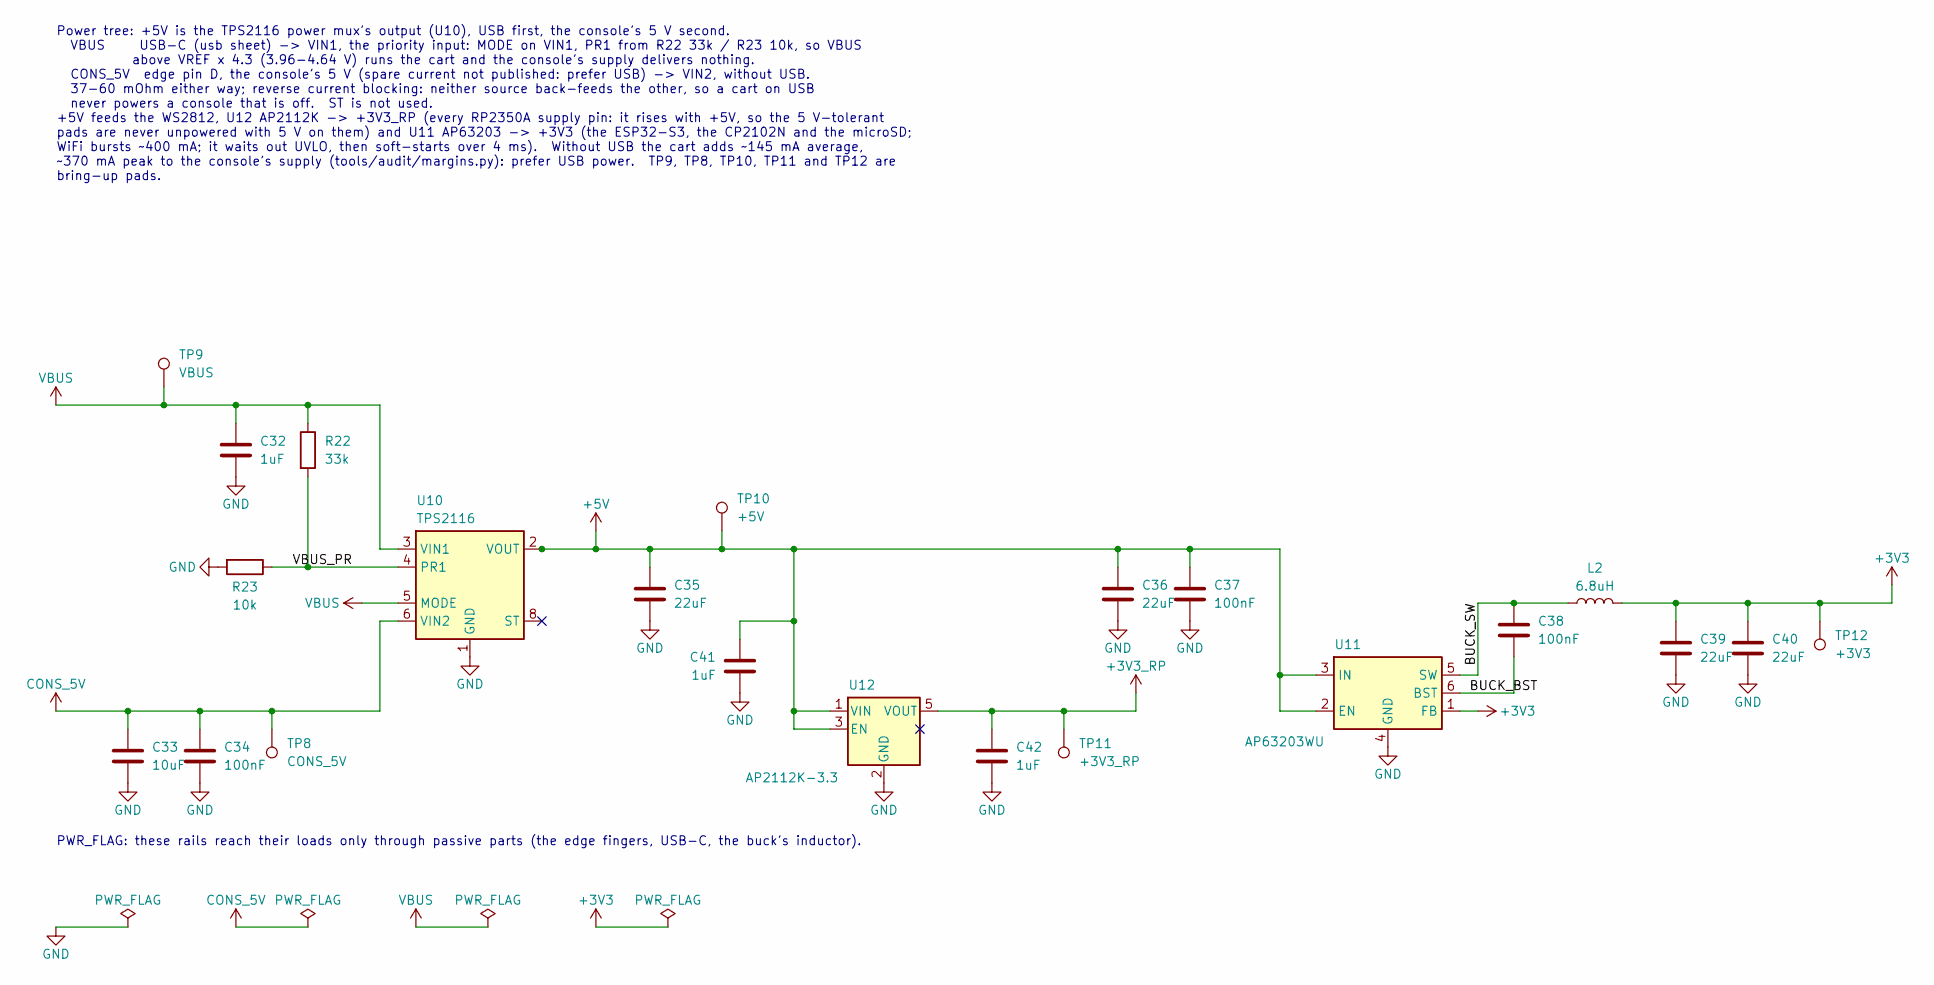
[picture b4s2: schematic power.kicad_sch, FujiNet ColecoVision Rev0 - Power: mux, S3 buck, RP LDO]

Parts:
C32, C41, C42: 1uF; C_0603_1608Metric; MPN CL10A105KB8NNNC; LCSC C15849
C33: 10uF; C_0603_1608Metric; MPN CL10A106KP8NNNC; LCSC C19702
C34, C37, C38: 100nF; C_0603_1608Metric; MPN CC0603KRX7R9BB104; LCSC C14663
C35, C36, C39, C40: 22uF; C_0805_2012Metric; MPN CL21A226MAQNNNE; LCSC C45783
L2: 6.8uH; L_Sunlord_SWPA4030S; MPN SWPA4030S6R8MT; LCSC C62684
R22: 33k; R_0603_1608Metric; MPN 0603WAF3302T5E; LCSC C4216
R23: 10k; R_0603_1608Metric; MPN 0603WAF1002T5E; LCSC C25804
TP8: CONS_5V; TestPoint_Pad_D1.5mm
TP9: VBUS; TestPoint_Pad_D1.5mm
TP10: +5V; TestPoint_Pad_D1.5mm
TP11: +3V3_RP; TestPoint_Pad_D1.5mm
TP12: +3V3; TestPoint_Pad_D1.5mm
U10: TPS2116; SOT-583-8; MPN TPS2116DRLR; LCSC C3235557
U11: AP63203WU; TSOT-23-6; MPN AP63203WU-7; LCSC C780769
U12: AP2112K-3.3; SOT-23-5; MPN AP2112K-3.3TRG1; LCSC C51118

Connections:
+3V3: C39.1, C40.1, L2.2, TP12.1, U11.1 (FB); also elsewhere on the board
+3V3_RP: C42.1, TP11.1, U12.5 (VOUT); also elsewhere on the board
+5V: C35.1, C36.1, C37.1, C41.1, TP10.1, U10.2 (VOUT), U10.7 (VOUT), U11.2 (EN), U11.3 (IN), U12.1 (VIN), U12.3 (EN); also elsewhere on the board
/power/BUCK_BST: C38.2, U11.6 (BST)
/power/BUCK_SW: C38.1, L2.1, U11.5 (SW)
/power/VBUS_PR: R22.2, R23.1, U10.4 (PR1)
CONS_5V: C33.1, C34.1, TP8.1, U10.6 (VIN2); also elsewhere on the board
GND: C32.2, C33.2, C34.2, C35.2, C36.2, C37.2, C39.2, C40.2, C41.2, C42.2, R23.2, U10.1 (GND), U11.4 (GND), U12.2 (GND); also elsewhere on the board
VBUS: C32.1, R22.1, TP9.1, U10.3 (VIN1), U10.5 (MODE); also elsewhere on the board

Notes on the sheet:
PWR_FLAG: these rails reach their loads only through passive parts (the edge fingers, USB-C, the buck's inductor).
Power tree: +5V is the TPS2116 power mux's output (U10), USB first, the console's 5 V second. VBUS USB-C (usb sheet) -> VIN1, the priority input: MODE on VIN1, PR1 from R22 33k / R23 10k, so VBUS above VREF x 4.3 (3.96-4.64 V) runs the cart and the console's supply delivers nothing. CONS_5V edge pi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
